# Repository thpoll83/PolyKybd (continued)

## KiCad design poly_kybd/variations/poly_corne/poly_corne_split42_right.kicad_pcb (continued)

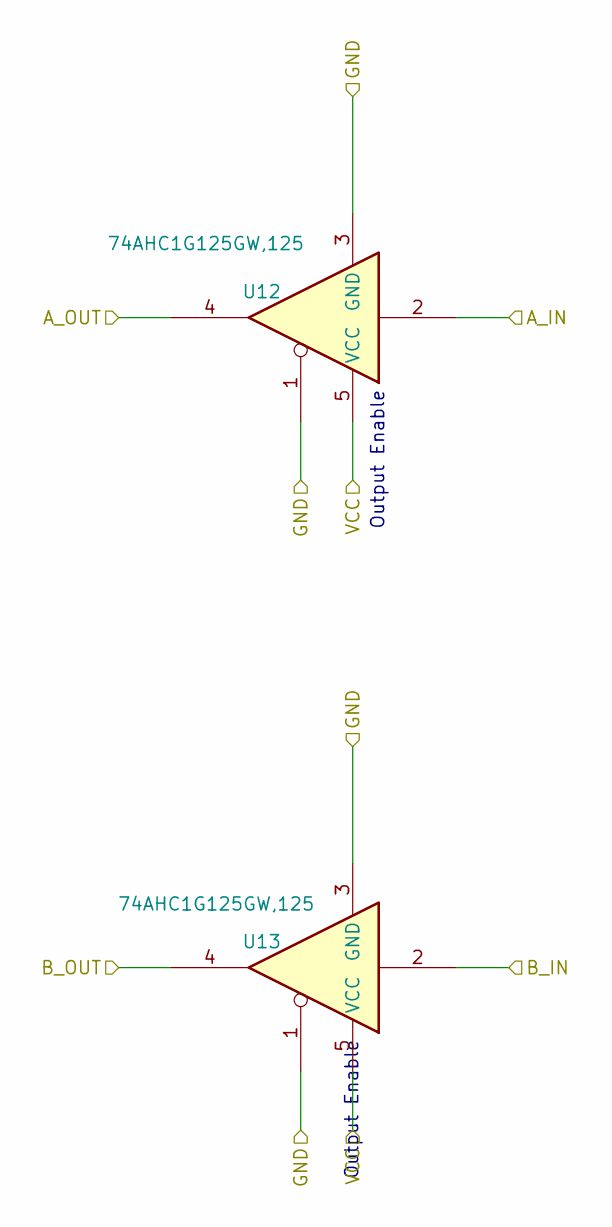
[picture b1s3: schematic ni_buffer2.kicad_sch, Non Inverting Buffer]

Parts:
U12, U13: 74AHC1G125GW,125; SOT-353_SC-70-5_Slim; MPN 74AHC1G125GW,125; JLC C85397

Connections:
/SCLK2: U13.4 (B); also elsewhere on the board
/SDIN2: U12.4 (B); also elsewhere on the board
GND: U12.1 (VCCA), U12.3 (GND), U13.1 (VCCA), U13.3 (GND); also elsewhere on the board
SCLK_RAW: U13.2 (A); also elsewhere on the board
SDIN_RAW: U12.2 (A); also elsewhere on the board
VDD: U12.5 (VCCB), U13.5 (VCCB); also elsewhere on the board

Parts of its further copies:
U14, U15, U16, U17, U18, U19, U20, U21, U22, U23: 74AHC1G125GW,125; SOT-353_SC-70-5_Slim; MPN 74AHC1G125GW,125; JLC C85397

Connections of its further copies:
/SCLK1: U15.4 (B); also elsewhere on the board
/SCLK3: U17.4 (B); also elsewhere on the board
/SCLK4: U19.4 (B); also elsewhere on the board
/SCLK5: U21.4 (B); also elsewhere on the board
/SCLK6: U23.4 (B); also elsewhere on the board
/SDIN1: U14.4 (B); also elsewhere on the board
/SDIN3: U16.4 (B); also elsewhere on the board
/SDIN4: U18.4 (B); also elsewhere on the board
/SDIN5: U20.4 (B); also elsewhere on the board
/SDIN6: U22.4 (B); also elsewhere on the board
GND: U14.1 (VCCA), U14.3 (GND), U15.1 (VCCA), U15.3 (GND), U16.1 (VCCA), U16.3 (GND), U17.1 (VCCA), U17.3 (GND), U18.1 (VCCA), U18.3 (GND), U19.1 (VCCA), U19.3 (GND), U20.1 (VCCA), U20.3 (GND), U21.1 (VCCA), U21.3 (GND), U22.1 (VCCA), U22.3 (GND), U23.1 (VCCA), U23.3 (GND); also elsewhere on the board
SCLK_RAW: U15.2 (A), U17.2 (A), U19.2 (A), U21.2 (A), U23.2 (A); also elsewhere on the board
SDIN_RAW: U14.2 (A), U16.2 (A), U18.2 (A), U20.2 (A), U22.2 (A); also elsewhere on the board
VDD: U14.5 (VCCB), U15.5 (VCCB), U16.5 (VCCB), U17.5 (VCCB), U18.5 (VCCB), U19.5 (VCCB), U20.5 (VCCB), U21.5 (VCCB), U22.5 (VCCB), U23.5 (VCCB); also elsewhere on the board

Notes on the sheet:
Output Enable

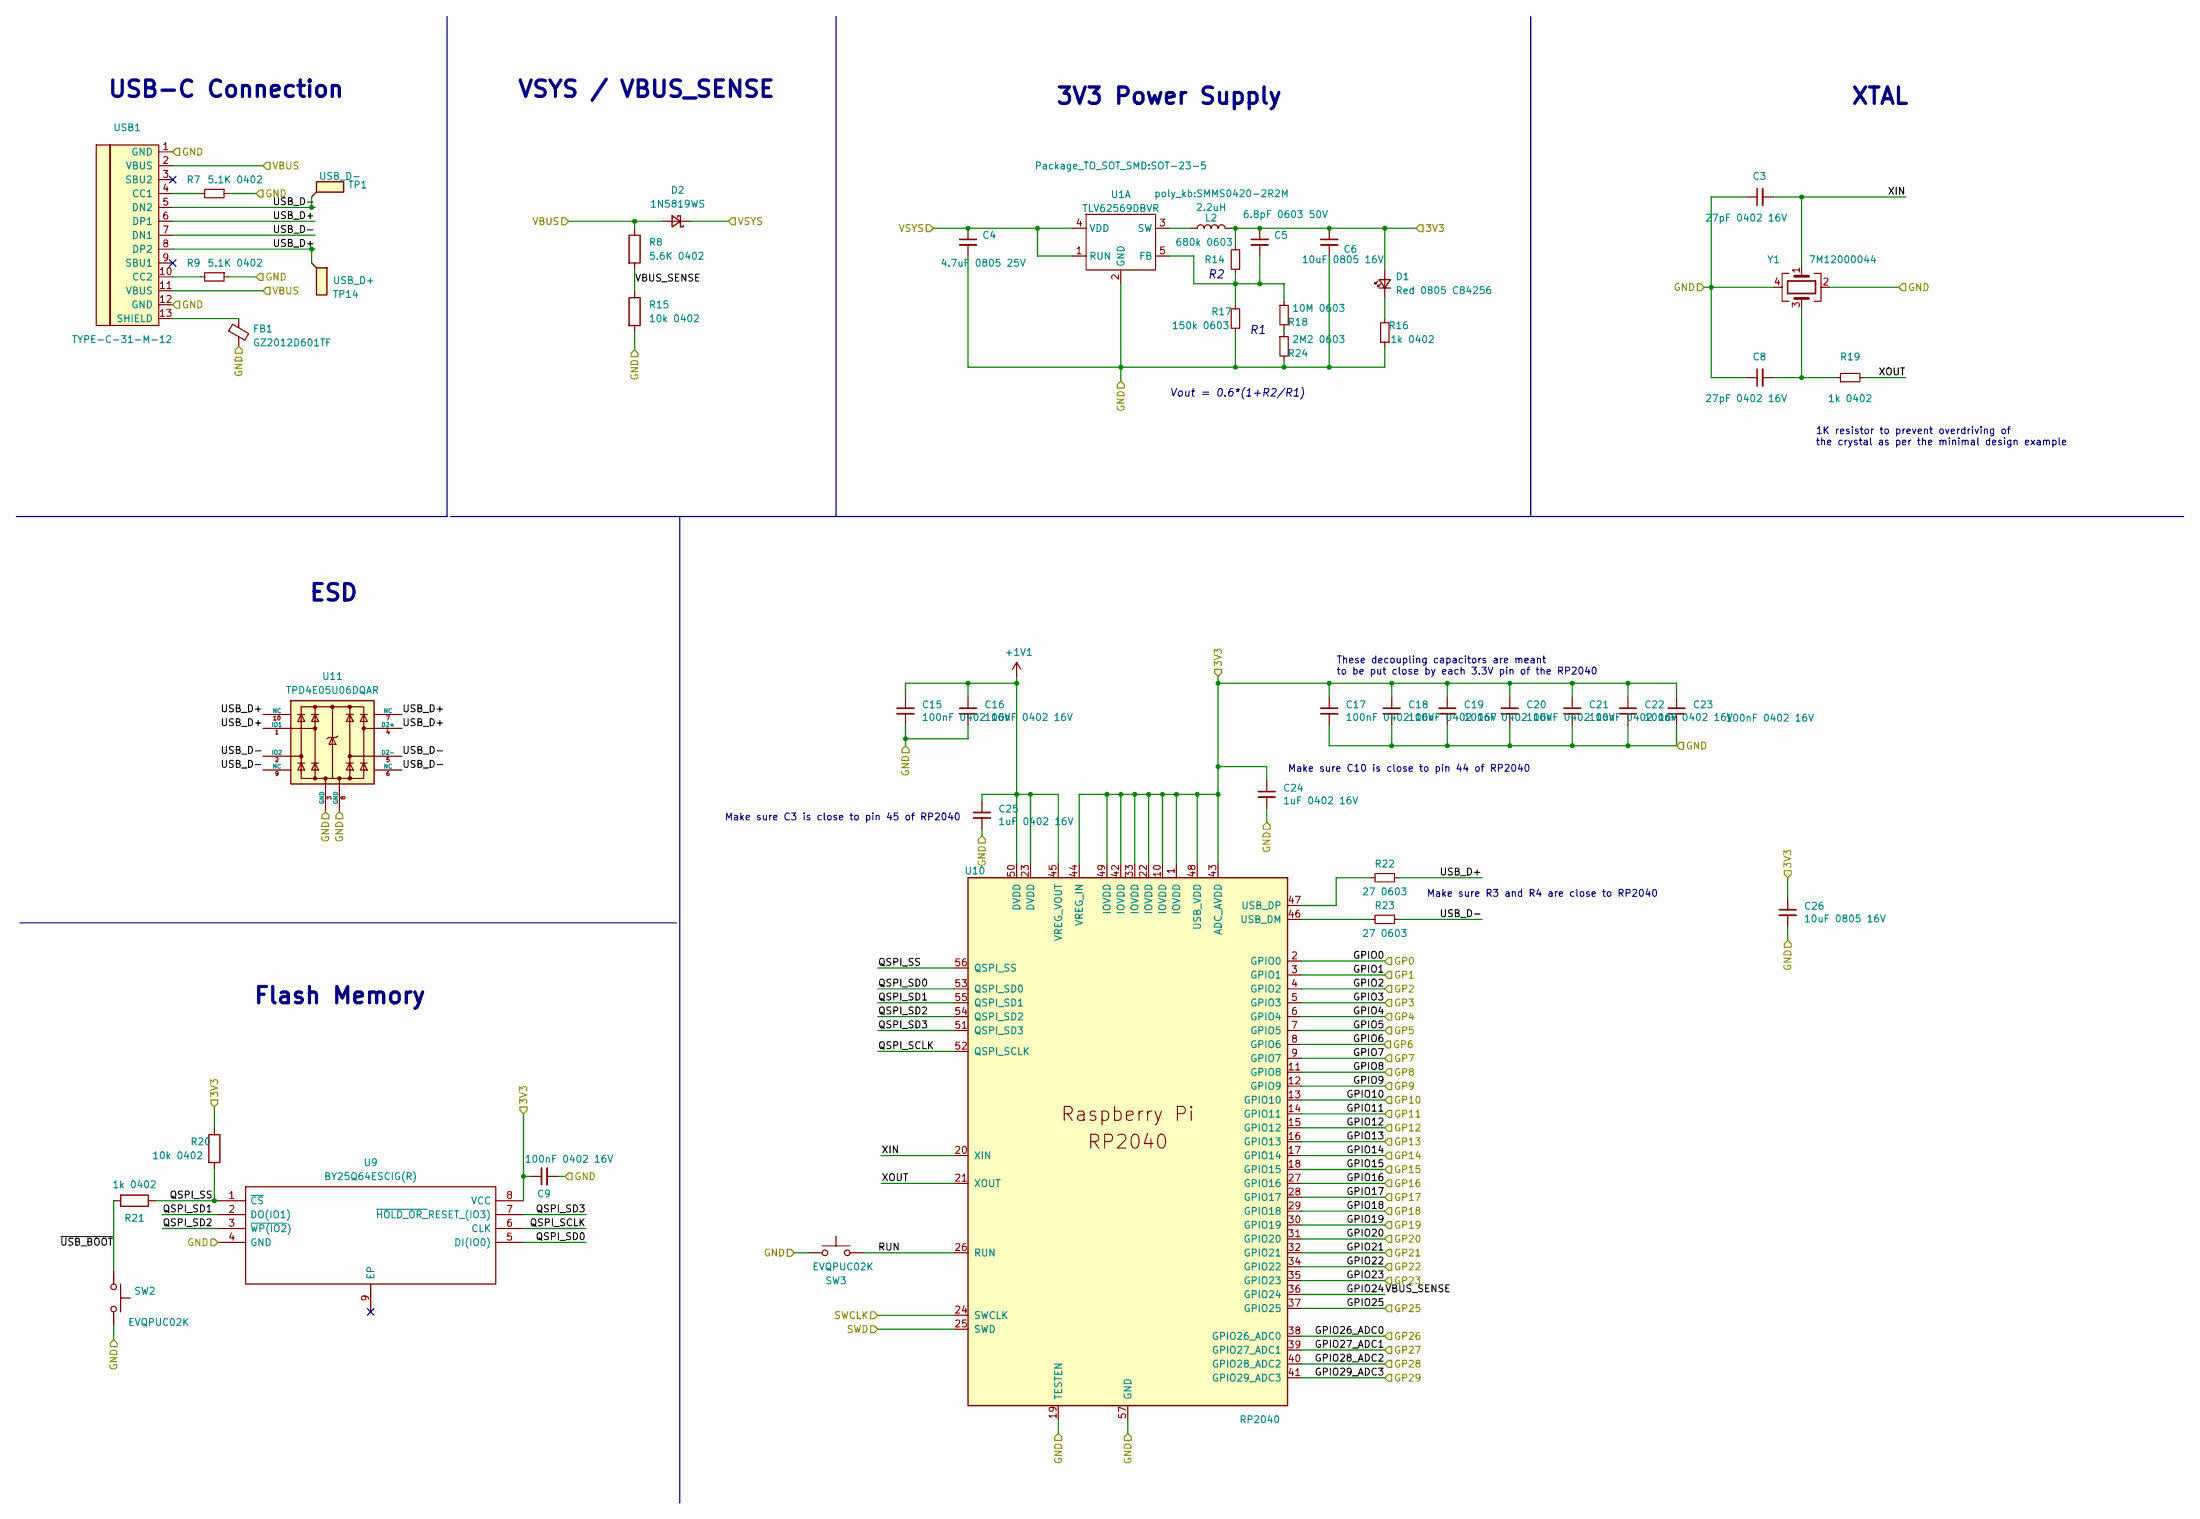
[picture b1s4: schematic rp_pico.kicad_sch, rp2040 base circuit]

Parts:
C3, C8: 27pF 0402 16V; C_0402_1005Metric; MPN C86287; JLC C86287
C4: 4.7uF 0805 25V; C_0805_2012Metric; MPN C1779; JLC C1779
C5: 6.8pF 0603 50V; C_0603_1608Metric; MPN CL10C6R8CB8NNNC; JLC C318672
C6, C26: 10uF 0805 16V; C_0805_2012Metric; MPN C15850; JLC C15850
C9, C15, C16, C17, C18, C19, C20, C21, C22, C23: 100nF 0402 16V; C_0402_1005Metric; MPN C1525; JLC C1525
C24, C25: 1uF 0402 16V; C_0402_1005Metric; MPN C52923; JLC C52923
D1: Red 0805 C84256; LED_0805_2012Metric; MPN C84256; JLC C84256
D2: 1N5819WS; D_SOD-323Ext; MPN C191023; JLC C191023
FB1: GZ2012D601TF; L_0805_2012Metric; MPN C1017; JLC C1017
L2: 2.2uH; SMMS0420-2R2M; MPN C133191; JLC C133191
R7, R9: 5.1K 0402; R_0402_1005Metric; MPN C144745; JLC C144745
R8: 5.6K 0402; R_0402_1005Metric; MPN C163457; JLC C163457
R14: 680k 0603; R_0603_1608Metric; MPN C137690; JLC C137690
R15, R20: 10k 0402; R_0402_1005Metric; MPN C60490; JLC C60490
R16, R19, R21: 1k 0402; R_0402_1005Metric; MPN CRCW04021K00FKED; JLC C71623
R17: 150k 0603; R_0603_1608Metric; MPN C114660; JLC C114660
R18: 10M 0603; R_0603_1608Metric; MPN C227547; JLC C227547
R22, R23: 27 0603; R_0603_1608Metric; MPN C137753; JLC C137753
R24: 2M2 0603; R_0603_1608Metric; MPN C137747; JLC C137747
SW2, SW3: EVQPUC02K; Panasonic_EVQPUL_EVQPUC; MPN C79174; JLC C79174
TP1: USB_D-; TestPoint_Pad_D1.5mm; MPN DNP; JLC DNP
TP14: USB_D+; TestPoint_Pad_D1.5mm; MPN DNP; JLC DNP
U1: TLV62569DBVR; SOT-23-5; MPN C141836; JLC C141836
U9: BY25Q64ESCIG(R); BY25Q64ES-LGA8-2x3; MPN BY25Q64ESCIG(R); JLC C50176394
U10: RP2040; RP2040-QFN-56; MPN C2040; JLC C2040
U11: TPD4E05U06DQAR; USON-10; MPN C2836386; JLC C2836386
USB1: TYPE-C-31-M-12; HRO-TYPE-C-31-M-12-Assembly; MPN C165948; JLC C165948
Y1: 7M12000044; Crystal_SMD_3225-4Pin_3.2x2.5mm; MPN C93114; JLC C93114

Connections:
+1V1: C15.1, C16.1, C25.1, U10.23 (DVDD), U10.45 (VREG_VOUT), U10.50 (DVDD)
/RpPico/GPIO6: U10.8 (GPIO6); also elsewhere on the board
/RpPico/GPIO7: U10.9 (GPIO7); also elsewhere on the board
/RpPico/GPIO24: R8.2, R15.1, U10.36 (GPIO24)
/RpPico/QSPI_SCLK: U9.6 (CLK), U10.52 (QSPI_SCLK)
/RpPico/QSPI_SD0: U9.5 (DI(IO0)), U10.53 (QSPI_SD0)
/RpPico/QSPI_SD1: U9.2 (DO(IO1)), U10.55 (QSPI_SD1)
/RpPico/QSPI_SD2: U9.3 (~WP(IO2)), U10.54 (QSPI_SD2)
/RpPico/QSPI_SD3: U9.7 (~HOLD_OR_RESET_(IO3)), U10.51 (QSPI_SD3)
/RpPico/QSPI_SS: R20.2, R21.1, U9.1 (~CS), U10.56 (QSPI_SS)
/RpPico/RUN: SW3.2, U10.26 (RUN)
/RpPico/SWCLK: U10.24 (SWCLK); also elsewhere on the board
/RpPico/SWD: U10.25 (SWD); also elsewhere on the board
/RpPico/USB_D+: R22.1, TP14.1, U11.1 (IO1), U11.4 (D2+), U11.7 (NC), U11.10 (NC), USB1.6 (DP1), USB1.8 (DP2)
/RpPico/USB_D-: R23.1, TP1.1, U11.2 (IO2), U11.5 (D2-), U11.6 (NC), U11.9 (NC), USB1.5 (DN2), USB1.7 (DN1)
/RpPico/XIN: C3.2, U10.20 (XIN), Y1.1
/RpPico/XOUT: R19.2, U10.21 (XOUT)
/RpPico/~USB_BOOT: R21.2, SW2.2
Col1: U10.13 (GPIO10); also elsewhere on the board
Col2: U10.14 (GPIO11); also elsewhere on the board
Col3: U10.15 (GPIO12); also elsewhere on the board
Col4: U10.16 (GPIO13); also elsewhere on the board
Col5: U10.17 (GPIO14); also elsewhere on the board
Col6: U10.18 (GPIO15); also elsewhere on the board
D-C: U10.11 (GPIO8); also elsewhere on the board
E0: U10.37 (GPIO25); also elsewhere on the board
E1: U10.41 (GPIO29_ADC3); also elsewhere on the board
E2: U10.27 (GPIO16); also elsewhere on the board
E3: U10.35 (GPIO23); also elsewhere on the board
E4: U10.34 (GPIO22); also elsewhere on the board
ENC_A: U10.4 (GPIO2); also elsewhere on the board
ENC_B: U10.5 (GPIO3); also elsewhere on the board
GND: C3.1, C4.2, C6.2, C8.1, C9.2, C15.2, C16.2, C17.2, C18.2, C19.2, C20.2, C21.2, C22.2, C23.2, C24.2, C25.2, C26.2, FB1.2, R7.1, R9.1, R15.2, R16.1, R17.1, R24.2, SW2.1, SW3.1, U1.2 (GND), U9.4 (GND), U9.9 (EP), U10.19 (TESTEN), U10.57 (GND), U11.3 (GND), U11.8 (GND), USB1.1 (GND), USB1.12 (GND), Y1.2, Y1.4; also elsewhere on the board
I2C_SCL: U10.3 (GPIO1); also elsewhere on the board
I2C_SDA: U10.2 (GPIO0); also elsewhere on the board
unnamed: C8.2, R19.1, Y1.3
unnamed: D1.1 (K), R16.2
unnamed: R18.2, R24.1
unnamed: C5.2, R14.1, R17.2, R18.1, U1.5 (FB)
unnamed: L2.1, U1.3 (SW)
unnamed: R23.2, U10.46 (USB_DM)
unnamed: R22.2, U10.47 (USB_DP)
unnamed: R7.2, USB1.4 (CC1)
unnamed: R9.2, USB1.10 (CC2)
unnamed: FB1.1, USB1.13 (SHIELD)
RESET: U10.12 (GPIO9); also elsewhere on the board
Row1: U10.29 (GPIO18); also elsewhere on the board
Row2: U10.30 (GPIO19); also elsewhere on the board
Row3: U10.31 (GPIO20); also elsewhere on the board
Row4: U10.32 (GPIO21); also elsewhere on the board
SERIAL_COM1: U10.6 (GPIO4); also elsewhere on the board
SERIAL_COM2: U10.7 (GPIO5); also elsewhere on the board
SPI0_CS_NC: U10.28 (GPIO17)
SR_CLOCK: U10.39 (GPIO27_ADC1); also elsewhere on the board
SR_DATA: U10.38 (GPIO26_ADC0); also elsewhere on the board
SR_LATCH: U10.40 (GPIO28_ADC2); also elsewhere on the board
VBUS: D2.2 (A), R8.1, USB1.2 (VBUS), USB1.11 (VBUS)
VDD: C5.1, C6.1, C9.1, C17.1, C18.1, C19.1, C20.1, C21.1, C22.1, C23.1, C24.1, C26.1, D1.2 (A), L2.2, R14.2, R20.1, U9.8 (VCC), U10.1 (IOVDD), U10.10 (IOVDD), U10.22 (IOVDD), U10.33 (IOVDD), U10.42 (IOVDD), U10.43 (ADC_AVDD), U10.44 (VREG_IN), U10.48 (USB_VDD), U10.49 (IOVDD); also elsewhere on the board
VSYS: C4.1, D2.1 (K), U1.1 (RUN), U1.4 (VDD); also elsewhere on the board

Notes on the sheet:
VSYS / VBUS_SENSE
Make sure R3 and R4 are close to RP2040
These decoupling capacitors are meant to be put close by each 3.3V pin of the RP2040
3V3 Power Supply
ESD
1K resistor to prevent overdriving of the crystal as per the minimal design example
Flash Memory
XTAL
Make sure C10 is close to pin 44 of RP2040
Make sure C3 is close to pin 45 of RP2040
Vout = 0.6*(1+R2/R1)
USB-C Connection

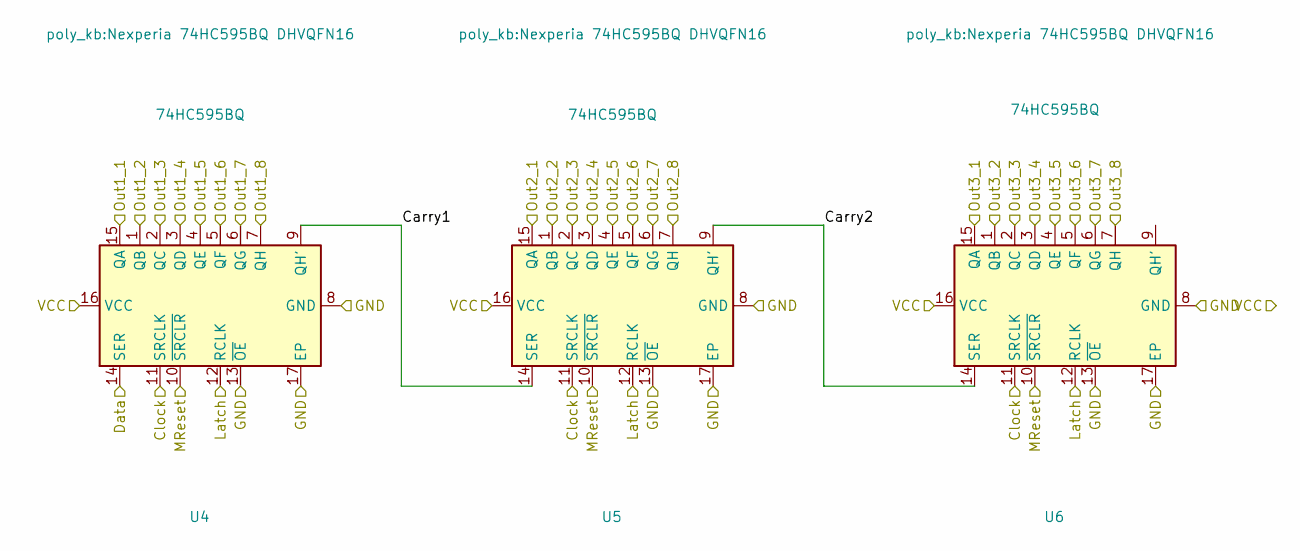
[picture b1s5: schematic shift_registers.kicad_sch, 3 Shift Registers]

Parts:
U4, U5, U6: 74HC595BQ; Nexperia 74HC595BQ DHVQFN16; MPN 74HC595BQ,115; JLC C730243

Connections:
/K_1/CS: U4.1 (QB); also elsewhere on the board
/K_2/CS: U4.2 (QC); also elsewhere on the board
/K_3/CS: U4.3 (QD); also elsewhere on the board
/K_4/CS: U4.4 (QE); also elsewhere on the board
/K_5/CS: U4.5 (QF); also elsewhere on the board
/K_A/CS: U6.1 (QB); also elsewhere on the board
/K_B/CS: U6.6 (QG); also elsewhere on the board
/K_C/CS: U4.6 (QG); also elsewhere on the board
/K_D/CS: U6.3 (QD); also elsewhere on the board
/K_E/CS: U5.3 (QD); also elsewhere on the board
/K_F/CS: U6.4 (QE); also elsewhere on the board
/K_G/CS: U6.5 (QF); also elsewhere on the board
/K_L1/CS: U4.15 (QA); also elsewhere on the board
/K_L2/CS: U5.15 (QA); also elsewhere on the board
/K_L3/CS: U6.15 (QA); also elsewhere on the board
/K_Q/CS: U5.1 (QB); also elsewhere on the board
/K_R/CS: U5.4 (QE); also elsewhere on the board
/K_S/CS: U6.2 (QC); also elsewhere on the board
/K_T/CS: U5.5 (QF); also elsewhere on the board
/K_V/CS: U5.6 (QG); also elsewhere on the board
/K_W/CS: U5.2 (QC); also elsewhere on the board
/ShiftRegisters/Carry1: U4.9 (QH'), U5.14 (SER)
/ShiftRegisters/Carry2: U5.9 (QH'), U6.14 (SER)
/ShiftRegisters/Out1_8: U4.7 (QH)
/ShiftRegisters/Out2_8: U5.7 (QH)
/ShiftRegisters/Out3_8: U6.7 (QH)
GND: U4.8 (GND), U4.13 (~OE), U4.17 (EP), U5.8 (GND), U5.13 (~OE), U5.17 (EP), U6.8 (GND), U6.13 (~OE), U6.17 (EP); also elsewhere on the board
RESET: U4.10 (~SRCLR), U5.10 (~SRCLR), U6.10 (~SRCLR); also elsewhere on the board
SR_CLOCK: U4.11 (SRCLK), U5.11 (SRCLK), U6.11 (SRCLK); also elsewhere on the board
SR_DATA: U4.14 (SER); also elsewhere on the board
SR_LATCH: U4.12 (RCLK), U5.12 (RCLK), U6.12 (RCLK); also elsewhere on the board
VDD: U4.16 (VCC), U5.16 (VCC), U6.16 (VCC); also elsewhere on the board

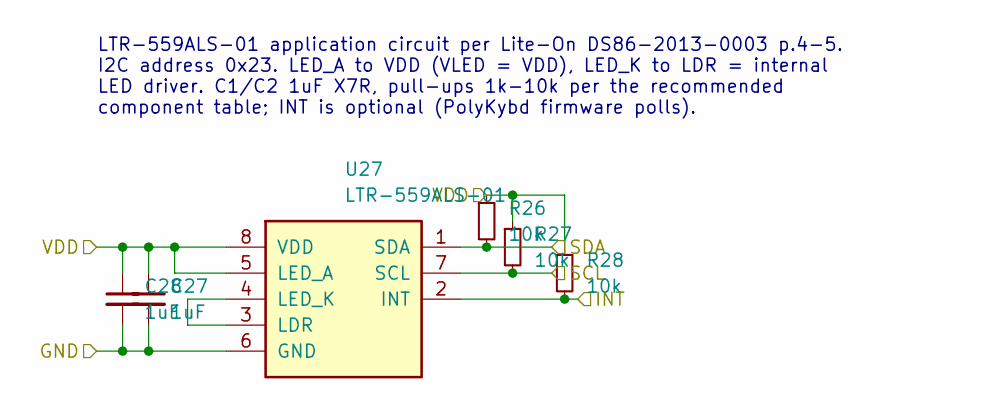
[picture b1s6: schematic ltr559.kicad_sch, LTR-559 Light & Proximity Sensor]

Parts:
C27, C28: 1uF
R26, R27, R28: 10k
U27: LTR-559ALS-01

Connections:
/LTR_INT: R28.2, U27.2 (INT)
GND: C27.2, C28.2, U27.6 (GND); also elsewhere on the board
I2C_SCL: R27.2, U27.7 (SCL); also elsewhere on the board
I2C_SDA: R26.2, U27.1 (SDA); also elsewhere on the board
unnamed: U27.3 (LDR), U27.4 (LED_K)
VDD: C27.1, C28.1, R26.1, R27.1, R28.1, U27.5 (LED_A), U27.8 (VDD); also elsewhere on the board

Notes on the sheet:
LTR-559ALS-01 application circuit per Lite-On DS86-2013-0003 p.4-5. I2C address 0x23. LED_A to VDD (VLED = VDD), LED_K to LDR = internal LED driver. C1/C2 1uF X7R, pull-ups 1k-10k per the recommended component table; INT is optional (PolyKybd firmware polls).

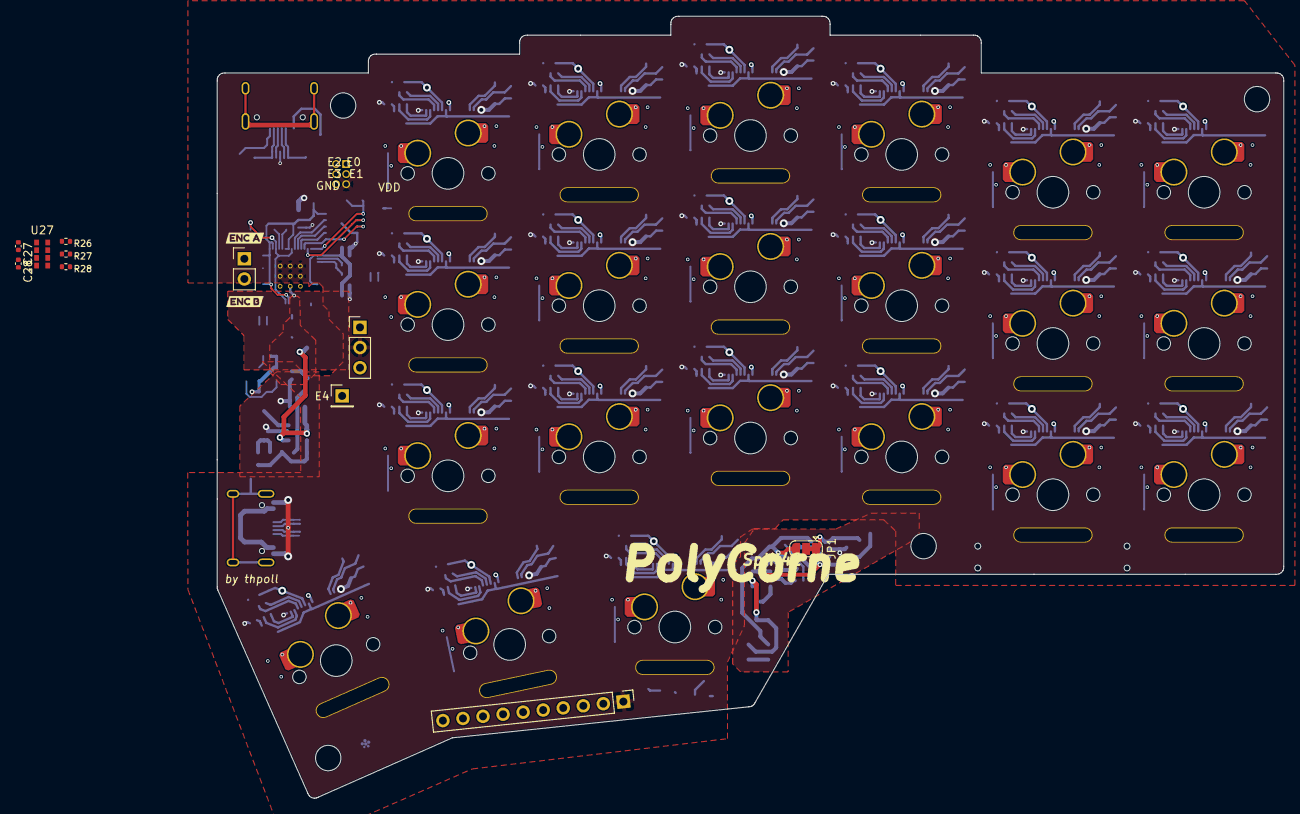
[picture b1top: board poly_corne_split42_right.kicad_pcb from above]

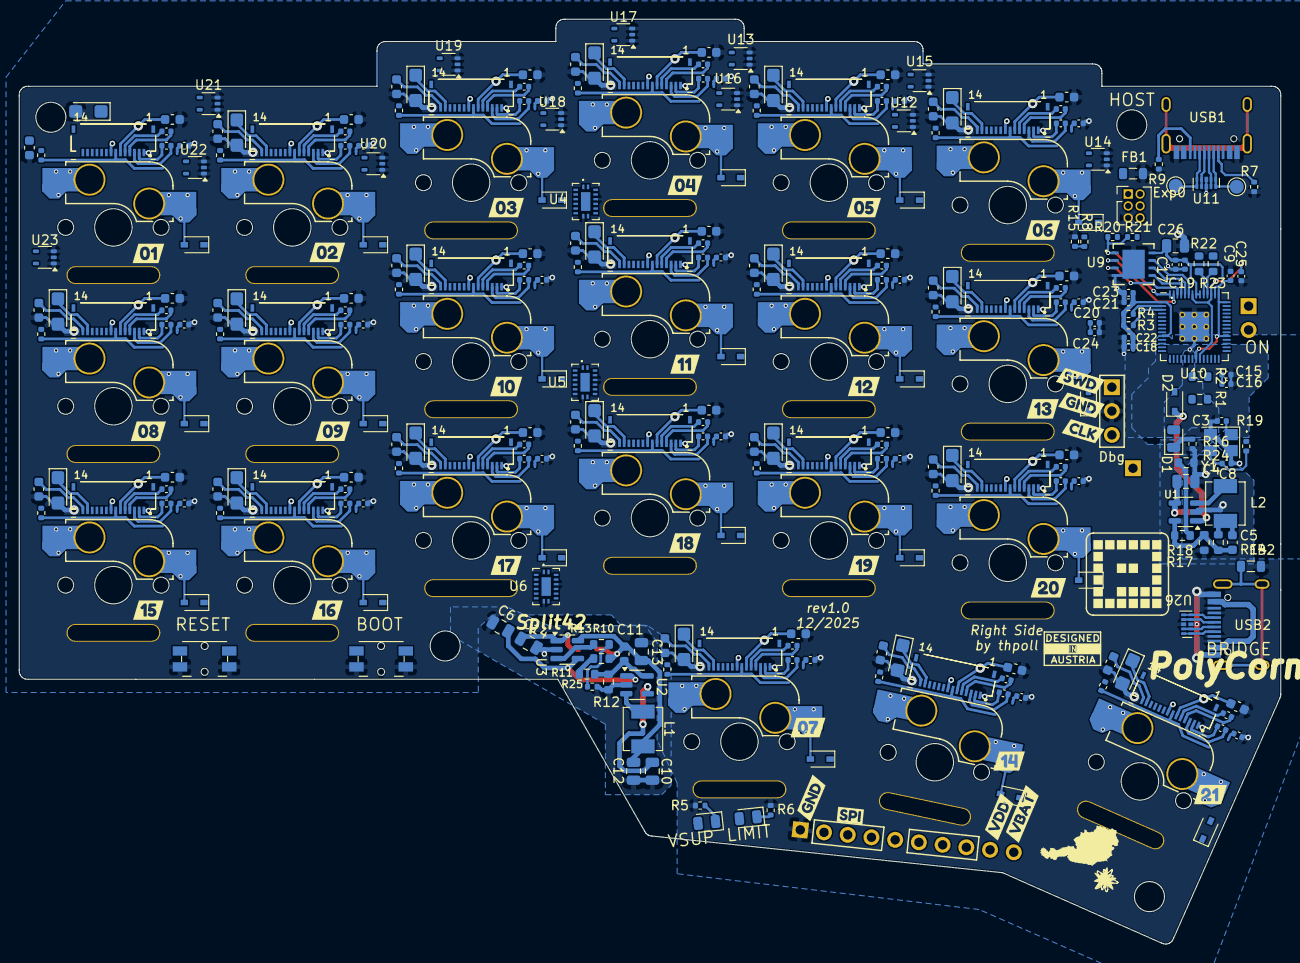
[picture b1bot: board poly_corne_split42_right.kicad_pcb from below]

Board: 4 copper layers, 134.3 x 98.5 mm, 337 parts (303 on the bottom side), 255 nets.

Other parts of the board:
kibuzzard-63EB51FD: G***; kibuzzard-63EB51FD
kibuzzard-639C2A93: G***; kibuzzard-639C2A93
kibuzzard-639C2D09: G***; kibuzzard-639C2D09
kibuzzard-639C2D25: G***; kibuzzard-639C2D25
kibuzzard-639C28BB, kibuzzard-639C28BB#2: G***; kibuzzard-639C28BB
kibuzzard-639C28CF: G***; kibuzzard-639C28CF
kibuzzard-639C34D4: G***; kibuzzard-639C34D4
kibuzzard-639C34FD: G***; kibuzzard-639C34FD
kibuzzard-639C35A2: G***; kibuzzard-639C35A2
kibuzzard-639C35AF: G***; kibuzzard-639C35AF
kibuzzard-639C35B8: G***; kibuzzard-639C35B8
kibuzzard-639C35C3: G***; kibuzzard-639C35C3
kibuzzard-639C35CB: G***; kibuzzard-639C35CB
kibuzzard-639C35DA: G***; kibuzzard-639C35DA
kibuzzard-639C35E7: G***; kibuzzard-639C35E7
kibuzzard-639C39A5: G***; kibuzzard-639C39A5
kibuzzard-639C294B: G***; kibuzzard-639C294B
kibuzzard-639C352E: G***; kibuzzard-639C352E
kibuzzard-639C353A: G***; kibuzzard-639C353A
kibuzzard-639C355D: G***; kibuzzard-639C355D
kibuzzard-639C357F: G***; kibuzzard-639C357F
kibuzzard-639C358A: G***; kibuzzard-639C358A
kibuzzard-639C3508: G***; kibuzzard-639C3508
kibuzzard-639C3514: G***; kibuzzard-639C3514
kibuzzard-639C3522: G***; kibuzzard-639C3522
kibuzzard-639C3548: G***; kibuzzard-639C3548
kibuzzard-639C3550: G***; kibuzzard-639C3550
kibuzzard-639C3575: G***; kibuzzard-639C3575
kibuzzard-639C3594: G***; kibuzzard-639C3594

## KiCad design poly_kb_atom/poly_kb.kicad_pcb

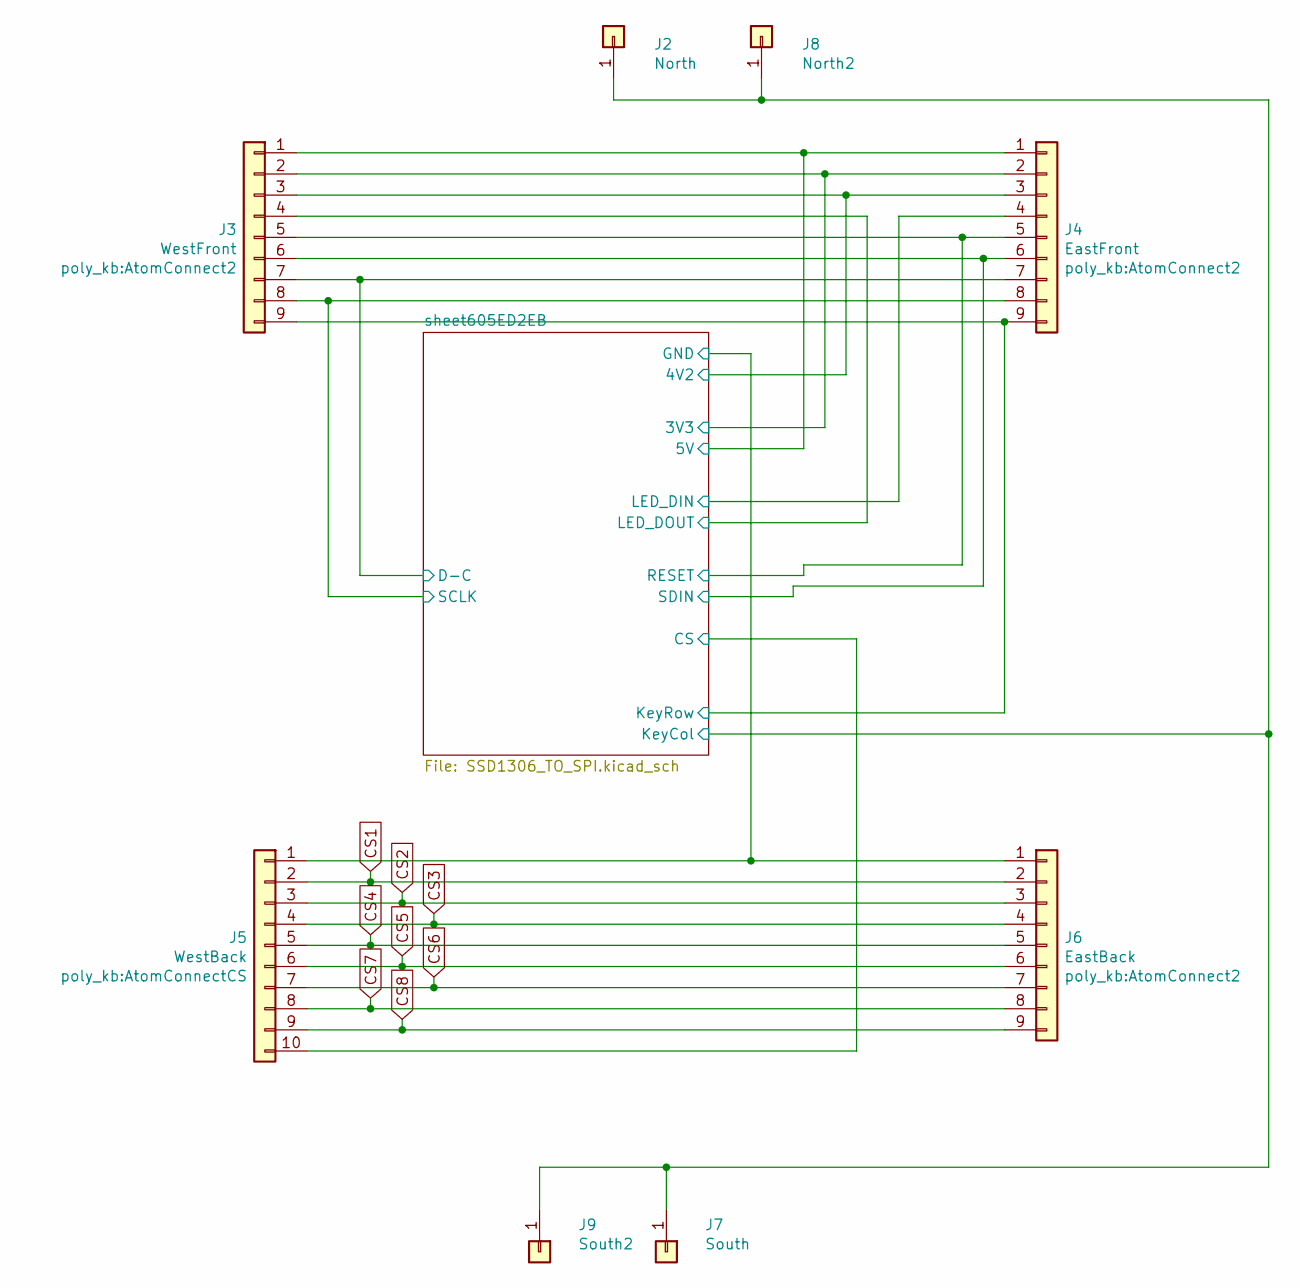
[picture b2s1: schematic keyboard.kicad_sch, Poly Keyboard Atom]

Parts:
J2: North; TestPoin_1.5x1.5mm_Drill0.7mm
J3: WestFront; AtomConnect2
J4: EastFront; AtomConnect2
J5: WestBack; AtomConnectCS
J6: EastBack; AtomConnect2
J7: South; TestPoin_1.5x1.5mm_Drill0.7mm
J8: North2; TestPoin_1.5x1.5mm_Drill0.7mm
J9: South2; TestPoin_1.5x1.5mm_Drill0.7mm

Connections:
/Keyboard/sheet605ED2EB/3V3: J3.2, J4.2; also elsewhere on the board
/Keyboard/sheet605ED2EB/4V2: J3.3, J4.3; also elsewhere on the board
/Keyboard/sheet605ED2EB/5V: J3.1, J4.1; also elsewhere on the board
/Keyboard/sheet605ED2EB/CS: J5.10; also elsewhere on the board
/Keyboard/sheet605ED2EB/D-C: J3.7, J4.7; also elsewhere on the board
/Keyboard/sheet605ED2EB/GND: J5.1, J6.1; also elsewhere on the board
/Keyboard/sheet605ED2EB/KeyCol: J2.1, J7.1, J8.1, J9.1; also elsewhere on the board
/Keyboard/sheet605ED2EB/KeyRow: J3.9, J4.9; also elsewhere on the board
/Keyboard/sheet605ED2EB/LED_DIN: J4.4; also elsewhere on the board
/Keyboard/sheet605ED2EB/LED_DOUT: J3.4; also elsewhere on the board
/Keyboard/sheet605ED2EB/RESET: J3.5, J4.5; also elsewhere on the board
/Keyboard/sheet605ED2EB/SCLK: J3.8, J4.8; also elsewhere on the board
/Keyboard/sheet605ED2EB/SDIN: J3.6, J4.6; also elsewhere on the board
CS1: J5.2, J6.2
CS2: J5.3, J6.3
CS3: J5.4, J6.4
CS4: J5.5, J6.5
CS5: J5.6, J6.6
CS6: J5.7, J6.7
CS7: J5.8, J6.8
CS8: J5.9, J6.9

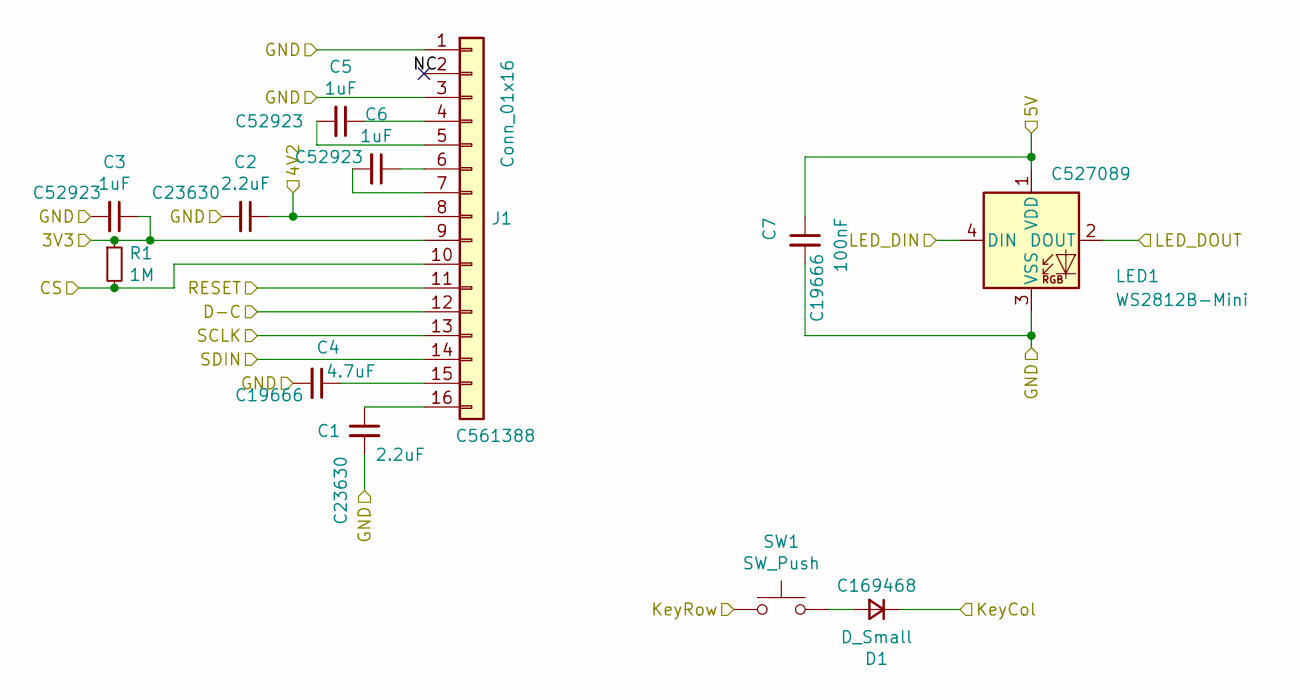
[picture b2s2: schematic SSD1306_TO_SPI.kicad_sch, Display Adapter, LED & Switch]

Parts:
C1, C2: 2.2uF; C_0603_1608Metric; LCSC C23630
C3, C5, C6: 1uF; C_0402_1005Metric; LCSC C52923
C4: 4.7uF; C_0603_1608Metric; LCSC C19666
C7: 100nF; C_0603_1608Metric; LCSC C19666
D1: D_Small; D_SOD-323Ext; LCSC C169468
J1: Conn_01x16; FPC_16_JUSHUO_AFC05_S16FIA_00; LCSC C561388
LED1: WS2812B-Mini; LCSC C527089
R1: 1M; R_0402_1005Metric
SW1: SW_Push; SW_Cherry_MX_1.00u_PCB_NoSilk

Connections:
/Keyboard/sheet605ED2EB/3V3: C3.1, J1.9, R1.1; also elsewhere on the board
/Keyboard/sheet605ED2EB/4V2: C2.1, J1.8; also elsewhere on the board
/Keyboard/sheet605ED2EB/5V: C7.1, LED1.1 (VDD); also elsewhere on the board
/Keyboard/sheet605ED2EB/CS: J1.10, R1.2; also elsewhere on the board
/Keyboard/sheet605ED2EB/D-C: J1.12; also elsewhere on the board
/Keyboard/sheet605ED2EB/GND: C1.2, C2.2, C3.2, C4.2, C7.2, J1.1, J1.3, LED1.3 (VSS); also elsewhere on the board
/Keyboard/sheet605ED2EB/KeyCol: D1.1 (K); also elsewhere on the board
/Keyboard/sheet605ED2EB/KeyRow: SW1.1; also elsewhere on the board
/Keyboard/sheet605ED2EB/LED_DIN: LED1.4 (DIN); also elsewhere on the board
/Keyboard/sheet605ED2EB/LED_DOUT: LED1.2 (DOUT); also elsewhere on the board
/Keyboard/sheet605ED2EB/RESET: J1.11; also elsewhere on the board
/Keyboard/sheet605ED2EB/SCLK: J1.13; also elsewhere on the board
/Keyboard/sheet605ED2EB/SDIN: J1.14; also elsewhere on the board
unnamed: C1.1, J1.16
unnamed: C4.1, J1.15
unnamed: C5.1, J1.4
unnamed: C5.2, J1.5
unnamed: C6.1, J1.6
unnamed: C6.2, J1.7
unnamed: D1.2 (A), SW1.2

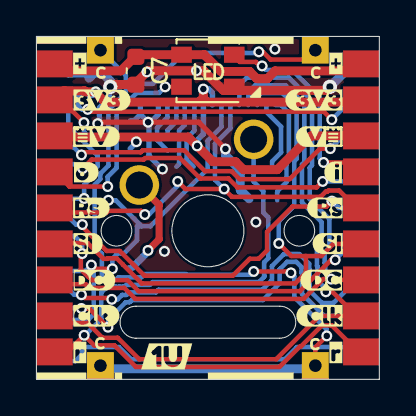
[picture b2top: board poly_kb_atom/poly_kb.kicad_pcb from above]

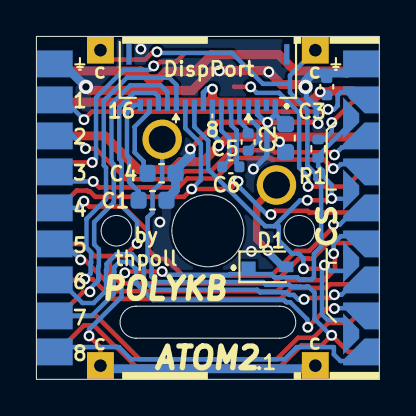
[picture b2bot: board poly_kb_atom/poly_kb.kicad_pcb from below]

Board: 2 copper layers, 19.0 x 19.0 mm, 39 parts (11 on the bottom side), 28 nets.

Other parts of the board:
kibuzzard-61EFA8F1: G***; kibuzzard-61EFA8F1
kibuzzard-61EFAA6D: G***; kibuzzard-61EFAA6D
kibuzzard-61EFABBF: G***; kibuzzard-61EFABBF
kibuzzard-61EFACF9: G***; kibuzzard-61EFACF9
kibuzzard-61EFBE2C: G***; kibuzzard-61EFBE2C
kibuzzard-61EFBE3D: G***; kibuzzard-61EFBE3D
kibuzzard-61EFBE21: G***; kibuzzard-61EFBE21
kibuzzard-61EFBE87: G***; kibuzzard-61EFBE87
kibuzzard-61EFD7F9: G***; kibuzzard-61EFD7F9
kibuzzard-61EFD863: G***; kibuzzard-61EFD863
kibuzzard-61EFD879: G***; kibuzzard-61EFD879
kibuzzard-61EFD908, kibuzzard-61EFD908#2: G***; kibuzzard-61EFD908
kibuzzard-61EFD947, kibuzzard-61EFD947#2: G***; kibuzzard-61EFD947
kibuzzard-61EFDAA0: G***; kibuzzard-61EFDAA0
kibuzzard-61EFDAC6: G***; kibuzzard-61EFDAC6
kibuzzard-61EFDAEE: G***; kibuzzard-61EFDAEE
kibuzzard-61EFDD1E: G***; kibuzzard-61EFDD1E

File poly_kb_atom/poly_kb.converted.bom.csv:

Designator,Quantity,Value,Footprint,LCSC Part #,Comment
"C1, C2",2,2.2uF,C_0603_1608Metric,C23630," Unpolarized capacitor, small symbol"
"C3, C5, C6",3,1uF,C_0402_1005Metric,C52923," Unpolarized capacitor, small symbol"
C4,1,4.7uF,C_0603_1608Metric,C19666," Unpolarized capacitor, small symbol"
D1,1,D_Small,D_SOD-323F,C2826370," Diode, small symbol"
J1,1,Conn_01x16,FPC_16_JUSHUO_AFC05_S16FIA_00,C561388," Generic connector, single row, 01x16, script generated (kicad-library-utils/schlib/autogen/connector/)"
J2,1,North,TestPoin_1.5x1.5mm_Drill0.7mm,," Generic connector, single row, 01x01, script generated (kicad-library-utils/schlib/autogen/connector/)"
J3,1,WestFront,AtomConnect2,," Generic connector, single row, 01x09, script generated (kicad-library-utils/schlib/autogen/connector/)"
J4,1,EastFront,AtomConnect2,," Generic connector, single row, 01x09, script generated (kicad-library-utils/schlib/autogen/connector/)"
J5,1,WestBack,AtomConnectCS,," Generic connector, single row, 01x10, script generated (kicad-library-utils/schlib/autogen/connector/)"
J6,1,EastBack,AtomConnect2,," Generic connector, single row, 01x09, script generated (kicad-library-utils/schlib/autogen/connector/)"
J7,1,South,TestPoin_1.5x1.5mm_Drill0.7mm,," Generic connector, single row, 01x01, script generated (kicad-library-utils/schlib/autogen/connector/)"
J8,1,North2,TestPoin_1.5x1.5mm_Drill0.7mm,," Generic connector, single row, 01x01, script generated (kicad-library-utils/schlib/autogen/connector/)"
J9,1,South2,TestPoin_1.5x1.5mm_Drill0.7mm,," Generic connector, single row, 01x01, script generated (kicad-library-utils/schlib/autogen/connector/)"
LED1,1,WS2812B-Mini,WS2812B-Mini,C527089, RGB LED with integrated controller
SW1,1,SW_Push,SW_Cherry_MX_1.00u_PCB_NoSilk,," Push button switch, generic, two pins"

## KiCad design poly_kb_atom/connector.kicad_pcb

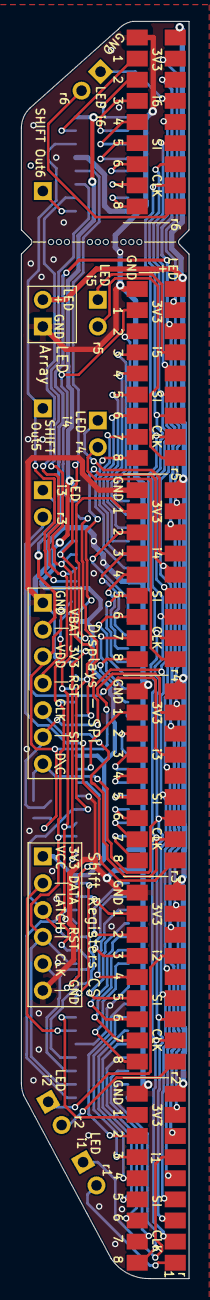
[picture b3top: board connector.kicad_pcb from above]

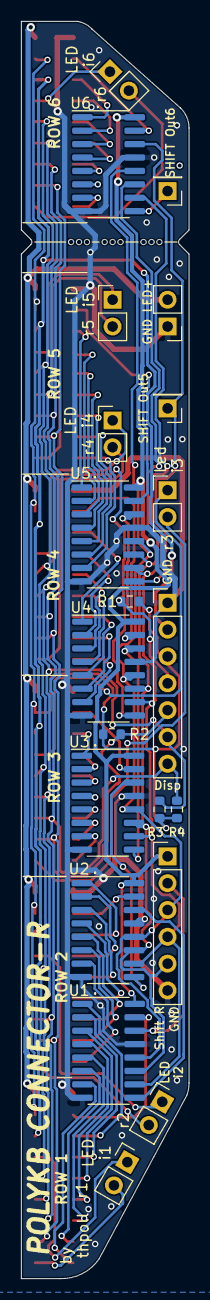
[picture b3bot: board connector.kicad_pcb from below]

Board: 2 copper layers, 15.9 x 119.0 mm, 36 parts (21 on the bottom side), 79 nets.

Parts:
J1, J2, J3, J4, J5, J6, J7, J8, J9, J10, J11, J12: Conn_01x09; AtomConnect2
J13: Conn_01x07; PinHeader_1x07_P2.54mm_Vertical
J14: Conn_01x06; PinHeader_1x06_P2.54mm_Vertical
J15, J17: Conn_01x01; PinHeader_1x01_P2.54mm_Vertical
J16, J21, J22, J23, J24, J25, J26: Conn_01x02; PinHeader_1x02_P2.54mm_Vertical
R1, R2, R3, R4: 1M; R_0603_1608Metric
U1, U2, U3, U4, U5, U6: 74HCT595; SOIC-16_3.9x9.9mm_P1.27mm
mouse-bite-2mm-slot, mouse-bite-2mm-slot#2, mouse-bite-2mm-slot#3: VAL**; mouse-bite-3x

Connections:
1: J1.2, U1.15
2: J1.3, U1.1
3: J1.4, U1.2
4: J1.5, U1.3
5: J1.6, U1.4
6: J1.7, U1.5
7: J1.8, U1.6
8: J1.9, U1.7
9: J3.2, U2.15
10: J3.3, U2.1
11: J3.4, U2.2
12: J3.5, U2.3
13: J3.6, U2.4
14: J3.7, U2.5
15: J3.8, U2.6
16: J3.9, U2.7
17: J5.2, U3.15
18: J5.3, U3.1
19: J5.4, U3.2
20: J5.5, U3.3
21: J5.6, U3.4
22: J5.7, U3.5
23: J5.8, U3.6
24: J5.9, U3.7
25: J7.2, U4.15
26: J7.3, U4.1
27: J7.4, U4.2
28: J7.5, U4.3
29: J7.6, U4.4
30: J7.7, U4.5
31: J7.8, U4.6
32: J7.9, U4.7
33: J9.2, U5.15
34: J9.3, U5.1
35: J9.4, U5.2
36: J9.5, U5.3
37: J9.6, U5.4
38: J9.7, U5.5
39: J9.8, U5.6
40: J9.9, U5.7
41: J11.2, U6.15
42: J11.3, U6.1
43: J11.4, U6.2
44: J11.5, U6.3
45: J11.6, U6.4
46: J11.7, U6.5
47: J11.8, U6.6
48: J11.9, U6.7
+3V3: J14.1, U1.16, U2.16, U3.16, U4.16, U5.16, U6.16
CLK: J2.8, J4.8, J6.8, J8.8, J10.8, J12.8, J13.5, R2.2
D\C: J2.7, J4.7, J6.7, J8.7, J10.7, J12.7, J13.7, R4.2
GND: J1.1, J3.1, J5.1, J7.1, J9.1, J11.1, J13.1, J14.6, J16.1, U1.8, U1.13, U2.8, U2.13, U3.8, U3.13, U4.8, U4.13, U5.8, U5.13, U6.8, U6.13
LedIn1: J2.4, J21.1
LedIn2: J4.4, J22.1
LedIn3: J6.4, J23.1
LedIn4: J8.4, J24.1
LedIn5: J10.4, J25.1
LedIn6: J12.4, J26.1
unnamed: U1.9, U2.14
unnamed: U2.9, U3.14
unnamed: U3.9, U4.14
unnamed: U4.9, U5.14
RST: J2.5, J4.5, J6.5, J8.5, J10.5, J12.5, J13.4, R1.2
SHIFTR_AOUT: J17.1, U5.9, U6.14
SHIFTR_CLK: J14.5, U1.11, U2.11, U3.11, U4.11, U5.11, U6.11
SHIFTR_DATA: J14.2, U1.14
SHIFTR_LATCH_CLK: J14.3, U1.12, U2.12, U3.12, U4.12, U5.12, U6.12
SHIFTR_OUT: J15.1, U6.9
SHIFTR_RST: J14.4, U1.10, U2.10, U3.10, U4.10, U5.10, U6.10
SI: J2.6, J4.6, J6.6, J8.6, J10.6, J12.6, J13.6, R3.2
VBAT: J2.3, J4.3, J6.3, J8.3, J10.3, J12.3, J13.2
VDD_3V3: J2.2, J4.2, J6.2, J8.2, J10.2, J12.2, J13.3, R1.1, R2.1, R3.1, R4.1
VLED: J2.1, J4.1, J6.1, J8.1, J10.1, J12.1, J16.2
r1: J2.9, J21.2
r2: J4.9, J22.2
r3: J6.9, J23.2
r4: J8.9, J24.2
r5: J10.9, J25.2
r6: J12.9, J26.2
